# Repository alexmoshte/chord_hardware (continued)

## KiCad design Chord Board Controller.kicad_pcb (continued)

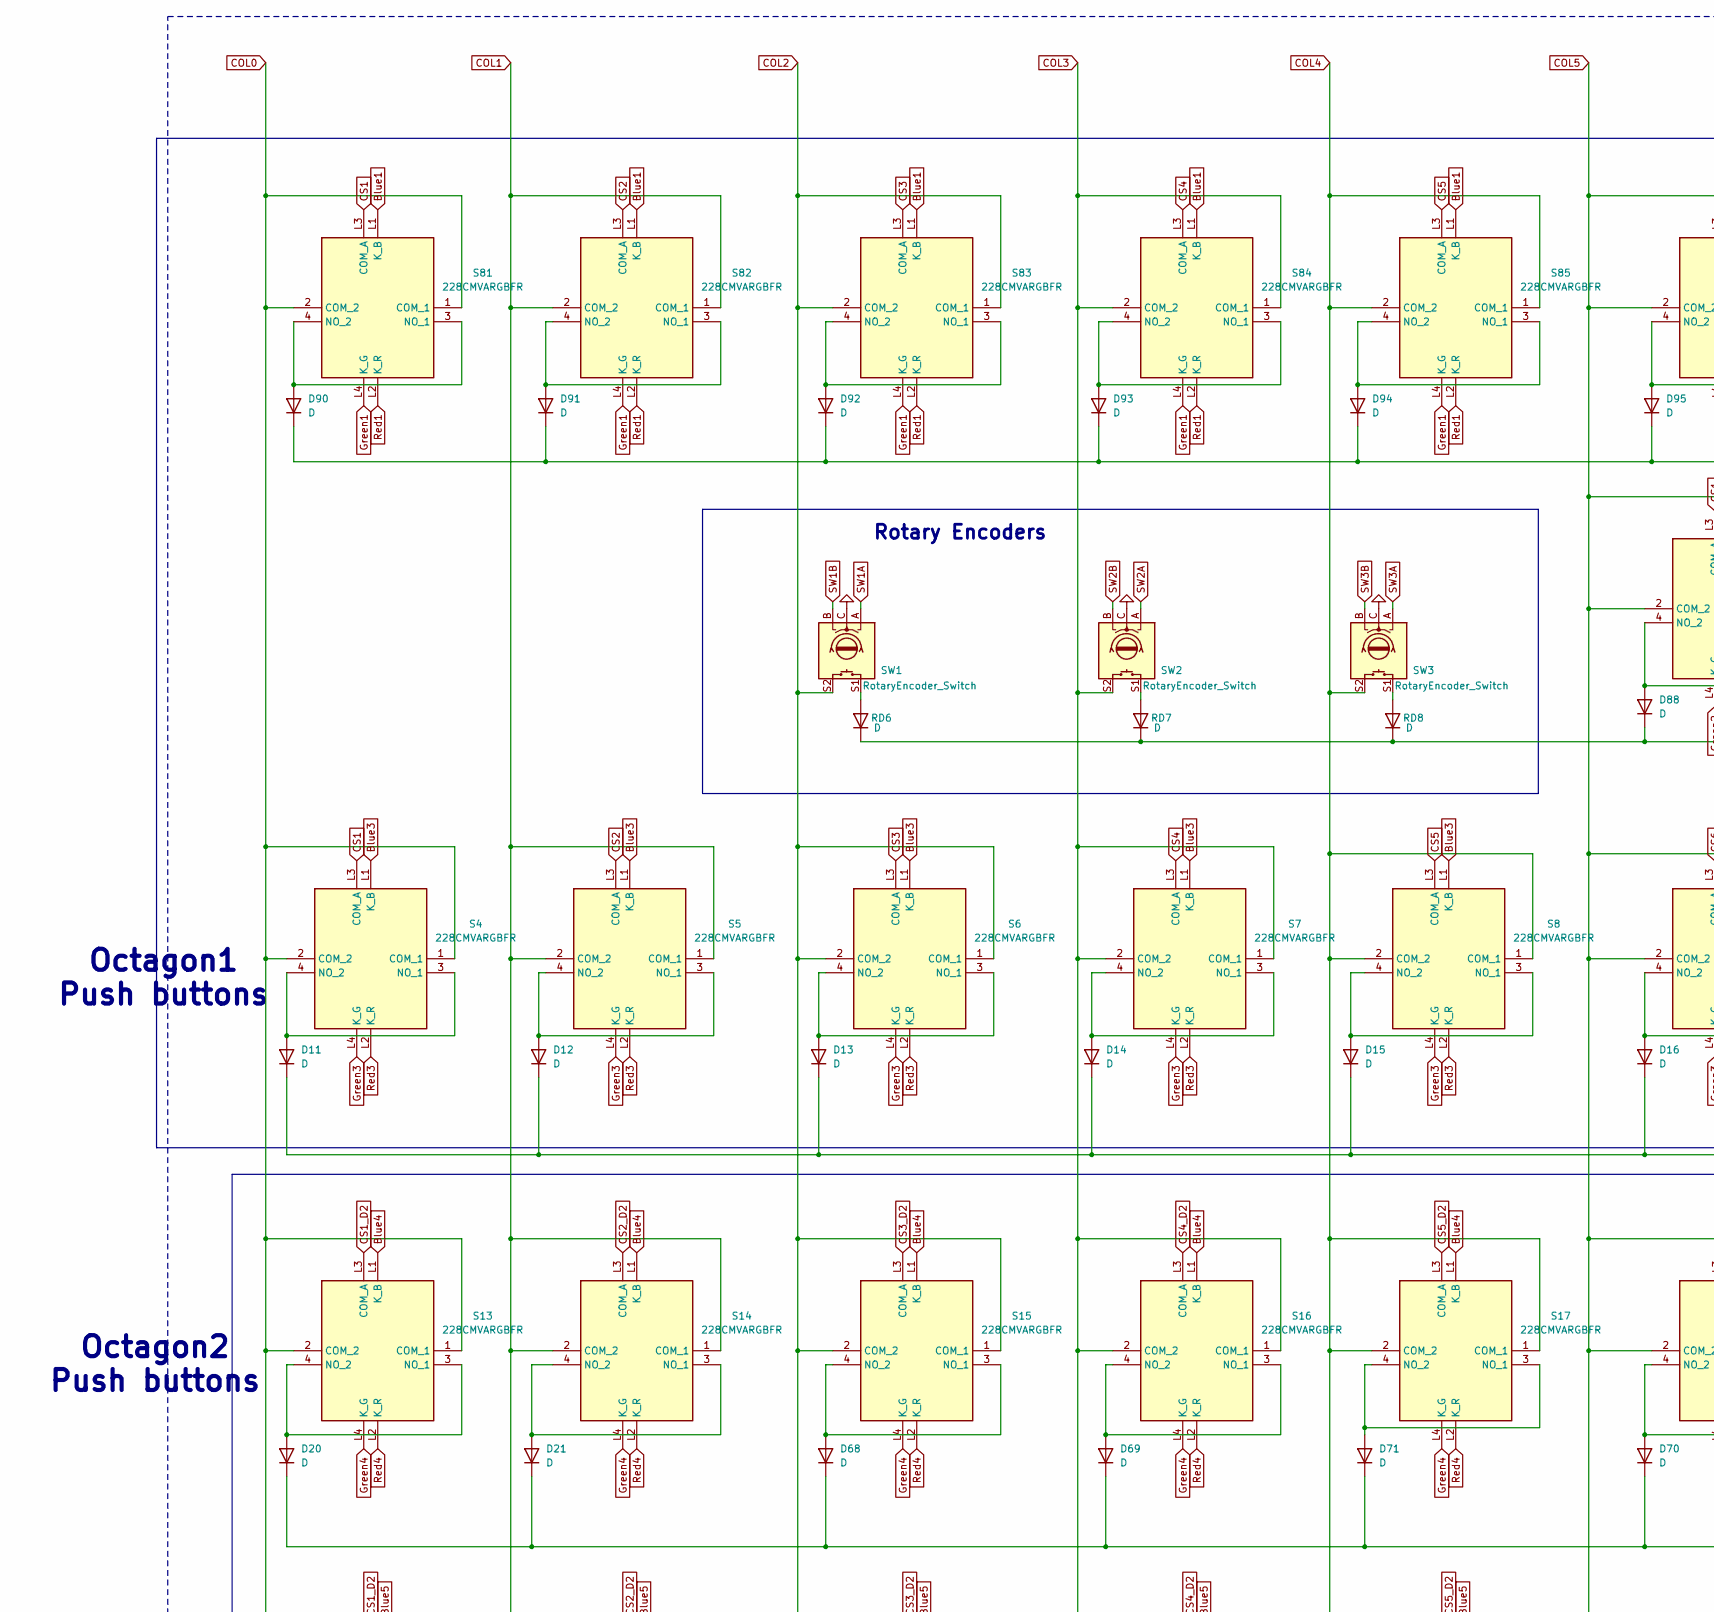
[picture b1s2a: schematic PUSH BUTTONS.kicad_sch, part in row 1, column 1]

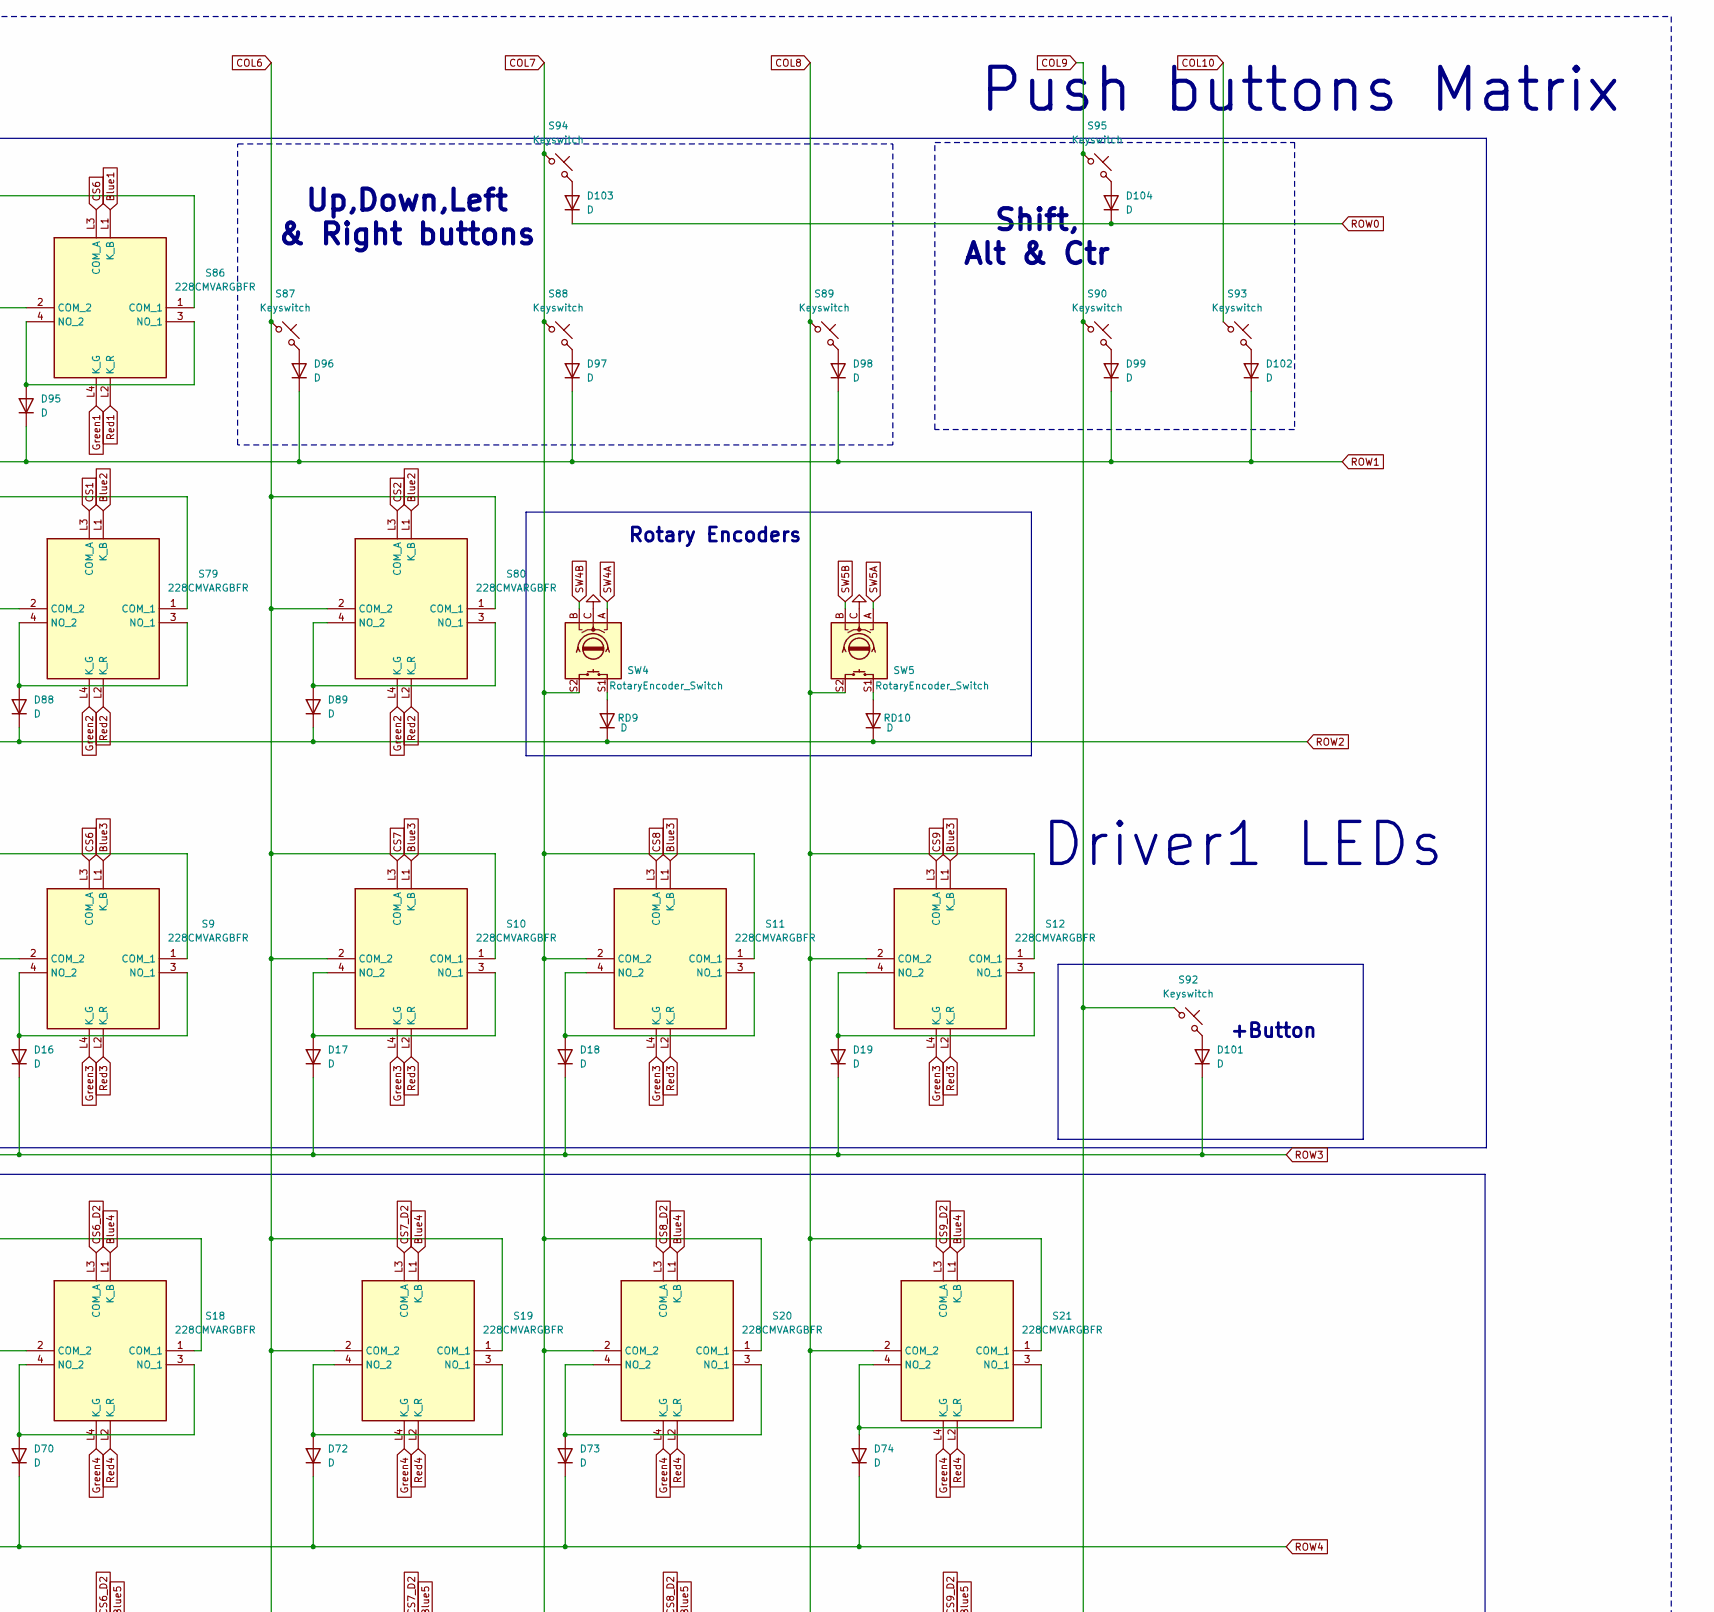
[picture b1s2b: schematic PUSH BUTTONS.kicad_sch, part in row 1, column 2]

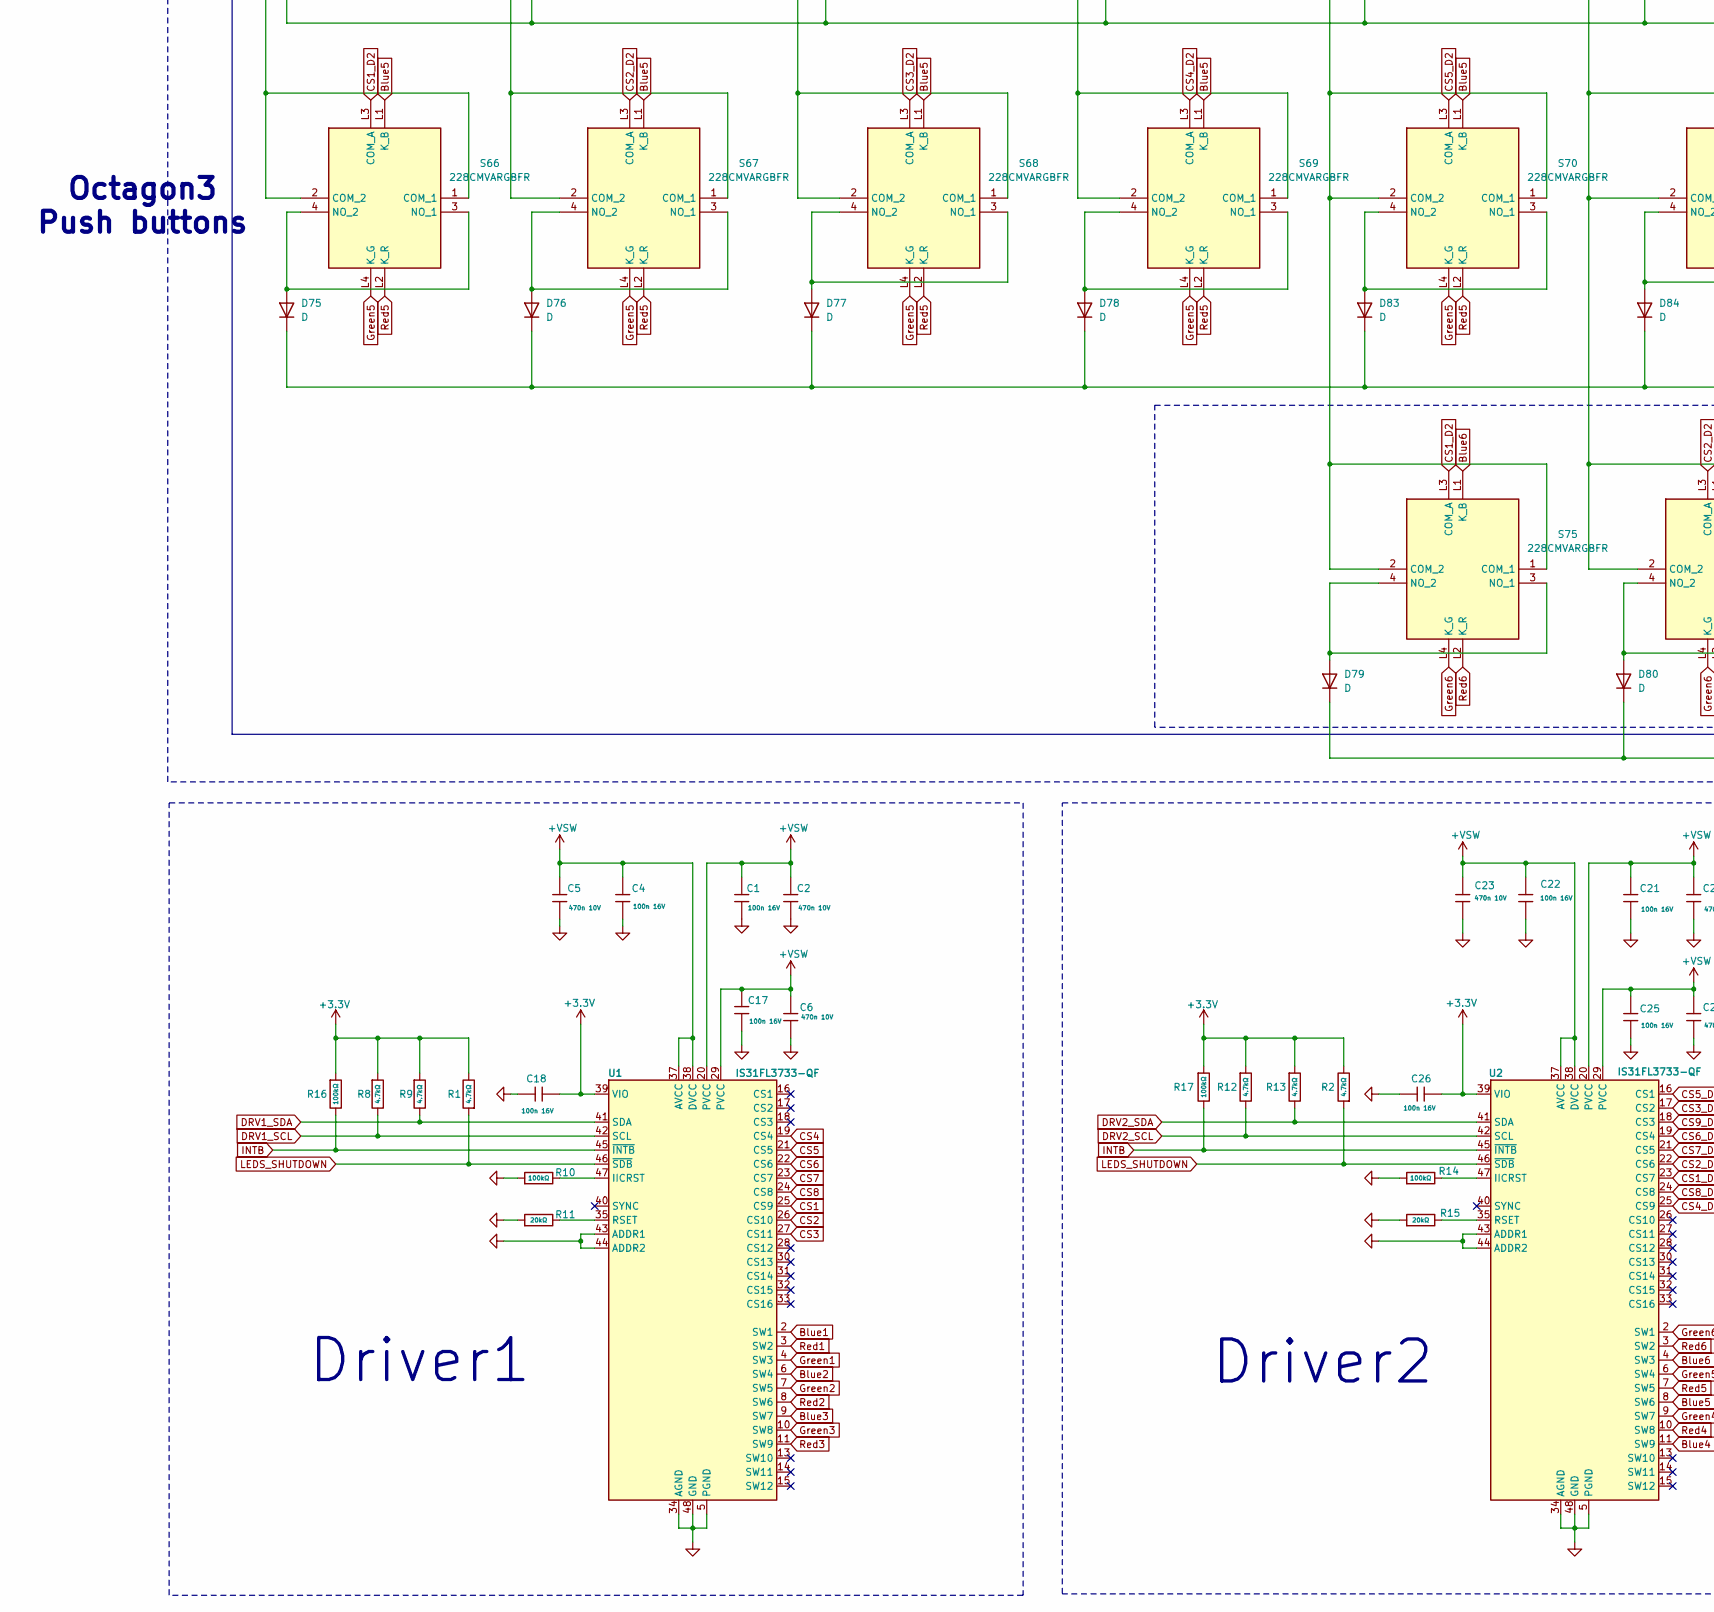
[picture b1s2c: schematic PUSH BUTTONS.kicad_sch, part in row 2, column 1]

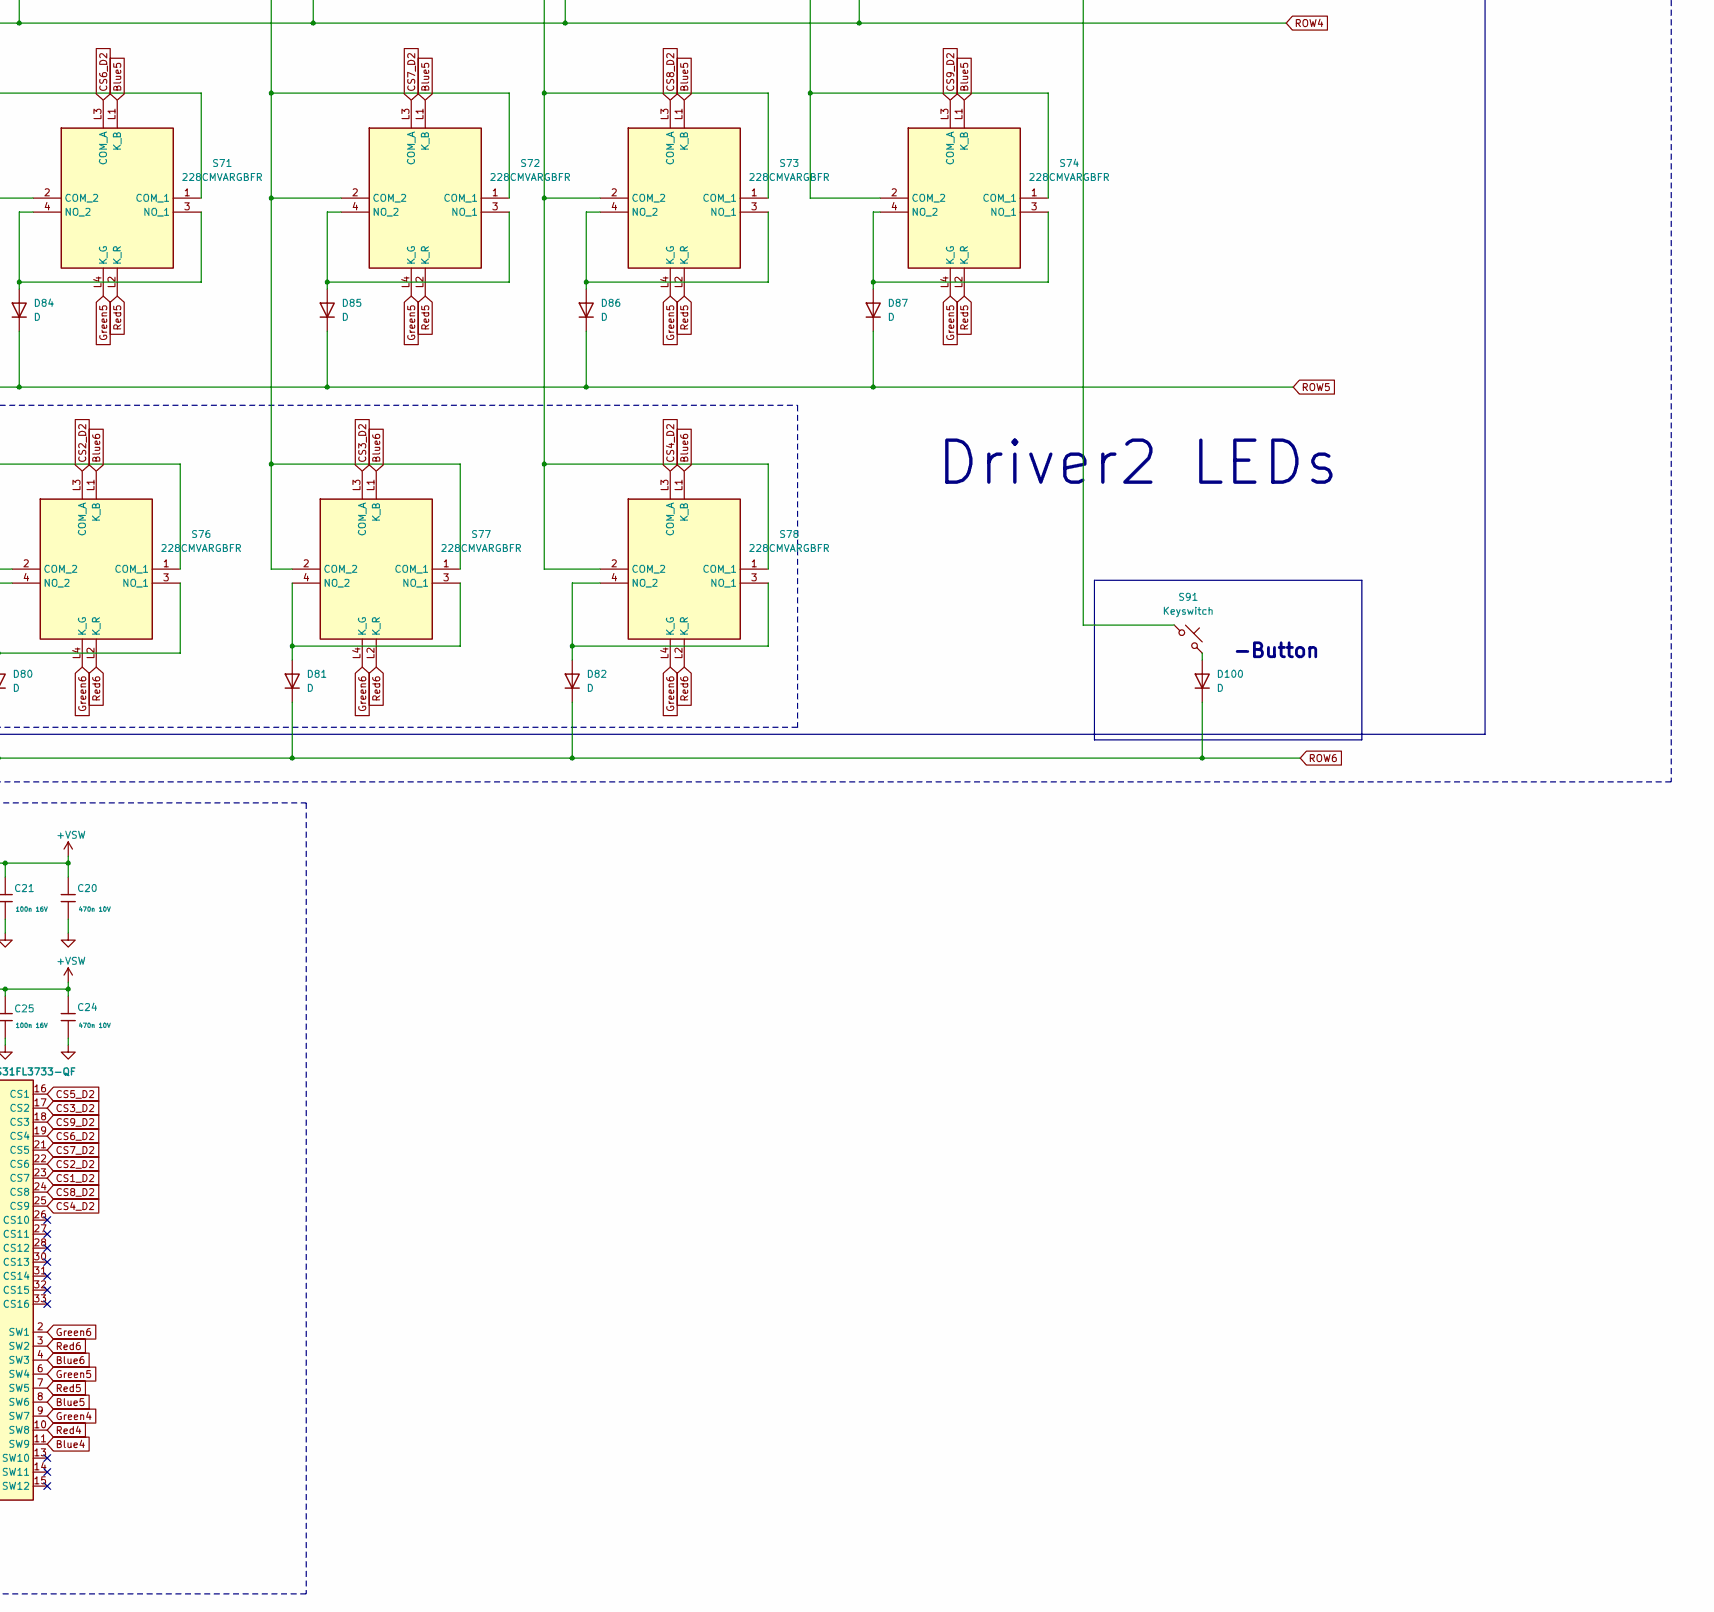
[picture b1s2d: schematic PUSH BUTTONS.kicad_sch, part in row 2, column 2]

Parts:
C1: 100n 16V; C_0603; Voltage Rated 6.3V; Tolerance ±20%; Part CL21A476MQYNNNE; LCSC C16780
C2, C5, C6, C20, C23, C24: 470n 10V; C_0402; Voltage Rated 10V; Tolerance ±10%; Part CL05A474KP5NNNC; LCSC C47339
C4, C17, C18, C21, C22, C25, C26: 100n 16V; C_0402; Voltage Rated 16V; Tolerance ±10%; Part CL05B104KO5NNNC; LCSC C1525
D11, D12, D13, D14, D15, D16, D17, D18, D19, D20, D21, D68, D69, D70, D71, D72, D73, D74, D75, D76, D77, D78, D79, D80, D81, D82, D83, D84, D85, D86, D87, D88, D89, D90, D91, D92, D93, D94, D95, D96, D97, D98, D99, D100, D101, D102, D103, D104: D; D_SOD-123; MFR.Part # SOD1F7; JLCPCB part# C33221
R1, R2, R8, R9, R12, R13: 4.7kΩ; R_0402; Overload Voltage (Max) 50V; Tolerance ±1%; Part 0402WGF4701TCE; LCSC C25900
R10, R14: 100kΩ; R_0402; Overload Voltage (Max) 50V; Tolerance ±1%; Part 0402WGF1003TCE; LCSC C25741
R11, R15: 20kΩ; R_0402; Overload Voltage (Max) 50V; Tolerance ±1%; Part 0402WGF2002TCE; LCSC C25765
R16, R17: 100kΩ; R_0603; Overload Voltage (Max) 75V; Tolerance ±1%; Part 0603WAF1003T5E; LCSC C25803
RD6, RD7, RD8, RD9, RD10: D; D_SOD-123
S4, S5, S6, S7, S8, S9, S10, S11, S12, S13, S14, S15, S16, S17, S18, S19, S20, S21, S66, S67, S68, S69, S70, S71, S72, S73, S74, S75, S76, S77, S78, S79, S80, S81, S82, S83, S84, S85, S86: 228CMVARGBFR; Mouser Part Number 774-228CMVARGBFR
S87, S88, S89, S90, S91, S92, S93, S94, S95: Keyswitch; SW_PUSH_6mm; MFR.Part # ZX-QC66-6.5CJ; JLCPCB part# C7470130
SW1, SW2, SW3, SW4, SW5: RotaryEncoder_Switch; ROT_Alps_EC11E-Switch
U1, U2: IS31FL3733-QF; QFN-48-1EP_6x6mm_P0.4mm_EP4.2x4.2mm

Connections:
+3.3V: C18.2, C26.2, R1.2, R2.2, R8.1, R9.1, R12.1, R13.1, R16.1, R17.1, U1.39 (VIO), U2.39 (VIO); also elsewhere on the board
+VSW: C1.1, C2.1, C4.1, C5.1, C6.1, C17.1, C20.1, C21.1, C22.1, C23.1, C24.1, C25.1, U1.20 (PVCC), U1.29 (PVCC), U1.37 (AVCC), U1.38 (DVCC), U2.20 (PVCC), U2.29 (PVCC), U2.37 (AVCC), U2.38 (DVCC); also elsewhere on the board
Blue1: S81.L1 (K_B), S82.L1 (K_B), S83.L1 (K_B), S84.L1 (K_B), S85.L1 (K_B), S86.L1 (K_B), U1.2 (SW1)
Blue2: S79.L1 (K_B), S80.L1 (K_B), U1.6 (SW4)
Blue3: S4.L1 (K_B), S5.L1 (K_B), S6.L1 (K_B), S7.L1 (K_B), S8.L1 (K_B), S9.L1 (K_B), S10.L1 (K_B), S11.L1 (K_B), S12.L1 (K_B), U1.9 (SW7)
Blue4: S13.L1 (K_B), S14.L1 (K_B), S15.L1 (K_B), S16.L1 (K_B), S17.L1 (K_B), S18.L1 (K_B), S19.L1 (K_B), S20.L1 (K_B), S21.L1 (K_B), U2.11 (SW9)
Blue5: S66.L1 (K_B), S67.L1 (K_B), S68.L1 (K_B), S69.L1 (K_B), S70.L1 (K_B), S71.L1 (K_B), S72.L1 (K_B), S73.L1 (K_B), S74.L1 (K_B), U2.8 (SW6)
Blue6: S75.L1 (K_B), S76.L1 (K_B), S77.L1 (K_B), S78.L1 (K_B), U2.4 (SW3)
COL0: S4.1 (COM_1), S4.2 (COM_2), S13.1 (COM_1), S13.2 (COM_2), S66.1 (COM_1), S66.2 (COM_2), S81.1 (COM_1), S81.2 (COM_2); also elsewhere on the board
COL1: S5.1 (COM_1), S5.2 (COM_2), S14.1 (COM_1), S14.2 (COM_2), S67.1 (COM_1), S67.2 (COM_2), S82.1 (COM_1), S82.2 (COM_2); also elsewhere on the board
COL2: S6.1 (COM_1), S6.2 (COM_2), S15.1 (COM_1), S15.2 (COM_2), S68.1 (COM_1), S68.2 (COM_2), S83.1 (COM_1), S83.2 (COM_2), SW1.S2; also elsewhere on the board
COL3: S7.1 (COM_1), S7.2 (COM_2), S16.1 (COM_1), S16.2 (COM_2), S69.1 (COM_1), S69.2 (COM_2), S84.1 (COM_1), S84.2 (COM_2), SW2.S2; also elsewhere on the board
COL4: S8.1 (COM_1), S8.2 (COM_2), S17.1 (COM_1), S17.2 (COM_2), S70.1 (COM_1), S70.2 (COM_2), S75.1 (COM_1), S75.2 (COM_2), S85.1 (COM_1), S85.2 (COM_2), SW3.S2; also elsewhere on the board
COL5: S9.1 (COM_1), S9.2 (COM_2), S18.1 (COM_1), S18.2 (COM_2), S71.1 (COM_1), S71.2 (COM_2), S76.1 (COM_1), S76.2 (COM_2), S79.1 (COM_1), S79.2 (COM_2), S86.1 (COM_1), S86.2 (COM_2); also elsewhere on the board
COL6: S10.1 (COM_1), S10.2 (COM_2), S19.1 (COM_1), S19.2 (COM_2), S72.1 (COM_1), S72.2 (COM_2), S77.1 (COM_1), S77.2 (COM_2), S80.1 (COM_1), S80.2 (COM_2), S87.1; also elsewhere on the board
COL7: S11.1 (COM_1), S11.2 (COM_2), S20.1 (COM_1), S20.2 (COM_2), S73.1 (COM_1), S73.2 (COM_2), S78.1 (COM_1), S78.2 (COM_2), S88.1, S94.1, SW4.S2; also elsewhere on the board
COL8: S12.1 (COM_1), S12.2 (COM_2), S21.1 (COM_1), S21.2 (COM_2), S74.1 (COM_1), S74.2 (COM_2), S89.1, SW5.S2; also elsewhere on the board
COL9: S90.1, S91.1, S92.1, S95.1; also elsewhere on the board
COL10: S93.1; also elsewhere on the board
CS1: S4.L3 (COM_A), S79.L3 (COM_A), S81.L3 (COM_A), U1.25 (CS9)
CS1_D2: S13.L3 (COM_A), S66.L3 (COM_A), S75.L3 (COM_A), U2.23 (CS7)
CS2: S5.L3 (COM_A), S80.L3 (COM_A), S82.L3 (COM_A), U1.26 (CS10)
CS2_D2: S14.L3 (COM_A), S67.L3 (COM_A), S76.L3 (COM_A), U2.22 (CS6)
CS3: S6.L3 (COM_A), S83.L3 (COM_A), U1.27 (CS11)
CS3_D2: S15.L3 (COM_A), S68.L3 (COM_A), S77.L3 (COM_A), U2.17 (CS2)
CS4: S7.L3 (COM_A), S84.L3 (COM_A), U1.19 (CS4)
CS4_D2: S16.L3 (COM_A), S69.L3 (COM_A), S78.L3 (COM_A), U2.25 (CS9)
CS5: S8.L3 (COM_A), S85.L3 (COM_A), U1.21 (CS5)
CS5_D2: S17.L3 (COM_A), S70.L3 (COM_A), U2.16 (CS1)
CS6: S9.L3 (COM_A), S86.L3 (COM_A), U1.22 (CS6)
CS6_D2: S18.L3 (COM_A), S71.L3 (COM_A), U2.19 (CS4)
CS7: S10.L3 (COM_A), U1.23 (CS7)
CS7_D2: S19.L3 (COM_A), S72.L3 (COM_A), U2.21 (CS5)
CS8: S11.L3 (COM_A), U1.24 (CS8)
CS8_D2: S20.L3 (COM_A), S73.L3 (COM_A), U2.24 (CS8)
CS9: S12.L3 (COM_A)
CS9_D2: S21.L3 (COM_A), S74.L3 (COM_A), U2.18 (CS3)
DRV1_SCL: R8.2, U1.42 (SCL); also elsewhere on the board
DRV1_SDA: R9.2, U1.41 (SDA); also elsewhere on the board
DRV2_SCL: R12.2, U2.42 (SCL); also elsewhere on the board
DRV2_SDA: R13.2, U2.41 (SDA); also elsewhere on the board
GND: C1.2, C2.2, C4.2, C5.2, C6.2, C17.2, C18.1, C20.2, C21.2, C22.2, C23.2, C24.2, C25.2, C26.1, R10.1, R11.1, R14.1, R15.1, SW1.C, SW2.C, SW3.C, SW4.C, SW5.C, U1.5 (PGND), U1.12 (PGND), U1.34 (AGND), U1.43 (ADDR1), U1.44 (ADDR2), U1.48 (GND), U1.49 (GND), U2.5 (PGND), U2.12 (PGND), U2.34 (AGND), U2.43 (ADDR1), U2.44 (ADDR2), U2.48 (GND), U2.49 (GND); also elsewhere on the board
Green1: S81.L4 (K_G), S82.L4 (K_G), S83.L4 (K_G), S84.L4 (K_G), S85.L4 (K_G), S86.L4 (K_G), U1.4 (SW3)
Green2: S79.L4 (K_G), S80.L4 (K_G), U1.7 (SW5)
Green3: S4.L4 (K_G), S5.L4 (K_G), S6.L4 (K_G), S7.L4 (K_G), S8.L4 (K_G), S9.L4 (K_G), S10.L4 (K_G), S11.L4 (K_G), S12.L4 (K_G), U1.10 (SW8)
Green4: S13.L4 (K_G), S14.L4 (K_G), S15.L4 (K_G), S16.L4 (K_G), S17.L4 (K_G), S18.L4 (K_G), S19.L4 (K_G), S20.L4 (K_G), S21.L4 (K_G), U2.9 (SW7)
Green5: S66.L4 (K_G), S67.L4 (K_G), S68.L4 (K_G), S69.L4 (K_G), S70.L4 (K_G), S71.L4 (K_G), S72.L4 (K_G), S73.L4 (K_G), S74.L4 (K_G), U2.6 (SW4)
Green6: S75.L4 (K_G), S76.L4 (K_G), S77.L4 (K_G), S78.L4 (K_G), U2.2 (SW1)
INTB: R16.2, R17.2, U1.45 (~INTB), U2.45 (~INTB); also elsewhere on the board
LEDS_SHUTDOWN: R1.1, R2.1, U1.46 (~SDB), U2.46 (~SDB); also elsewhere on the board
unnamed: D11.2 (A), S4.3 (NO_1), S4.4 (NO_2)
unnamed: D12.2 (A), S5.3 (NO_1), S5.4 (NO_2)
unnamed: D13.2 (A), S6.3 (NO_1), S6.4 (NO_2)
unnamed: D14.2 (A), S7.3 (NO_1), S7.4 (NO_2)
unnamed: D15.2 (A), S8.3 (NO_1), S8.4 (NO_2)
unnamed: D16.2 (A), S9.3 (NO_1), S9.4 (NO_2)
unnamed: D17.2 (A), S10.3 (NO_1), S10.4 (NO_2)
unnamed: D18.2 (A), S11.3 (NO_1), S11.4 (NO_2)
unnamed: D19.2 (A), S12.3 (NO_1), S12.4 (NO_2)
unnamed: D20.2 (A), S13.3 (NO_1), S13.4 (NO_2)
unnamed: D21.2 (A), S14.3 (NO_1), S14.4 (NO_2)
unnamed: D68.2 (A), S15.3 (NO_1), S15.4 (NO_2)
unnamed: D69.2 (A), S16.3 (NO_1), S16.4 (NO_2)
unnamed: D70.2 (A), S18.3 (NO_1), S18.4 (NO_2)
unnamed: D71.2 (A), S17.3 (NO_1), S17.4 (NO_2)
unnamed: D72.2 (A), S19.3 (NO_1), S19.4 (NO_2)
unnamed: D73.2 (A), S20.3 (NO_1), S20.4 (NO_2)
unnamed: D74.2 (A), S21.3 (NO_1), S21.4 (NO_2)
unnamed: D75.2 (A), S66.3 (NO_1), S66.4 (NO_2)
unnamed: D76.2 (A), S67.3 (NO_1), S67.4 (NO_2)
unnamed: D77.2 (A), S68.3 (NO_1), S68.4 (NO_2)
unnamed: D78.2 (A), S69.3 (NO_1), S69.4 (NO_2)
unnamed: D79.2 (A), S75.3 (NO_1), S75.4 (NO_2)
unnamed: D80.2 (A), S76.3 (NO_1), S76.4 (NO_2)
unnamed: D81.2 (A), S77.3 (NO_1), S77.4 (NO_2)
unnamed: D82.2 (A), S78.3 (NO_1), S78.4 (NO_2)
unnamed: D83.2 (A), S70.3 (NO_1), S70.4 (NO_2)
unnamed: D84.2 (A), S71.3 (NO_1), S71.4 (NO_2)
unnamed: D85.2 (A), S72.3 (NO_1), S72.4 (NO_2)
unnamed: D86.2 (A), S73.3 (NO_1), S73.4 (NO_2)
unnamed: D87.2 (A), S74.3 (NO_1), S74.4 (NO_2)
unnamed: D88.2 (A), S79.3 (NO_1), S79.4 (NO_2)
unnamed: D89.2 (A), S80.3 (NO_1), S80.4 (NO_2)
unnamed: D90.2 (A), S81.3 (NO_1), S81.4 (NO_2)
unnamed: D91.2 (A), S82.3 (NO_1), S82.4 (NO_2)
unnamed: D92.2 (A), S83.3 (NO_1), S83.4 (NO_2)
unnamed: D93.2 (A), S84.3 (NO_1), S84.4 (NO_2)
unnamed: D94.2 (A), S85.3 (NO_1), S85.4 (NO_2)
unnamed: D95.2 (A), S86.3 (NO_1), S86.4 (NO_2)
unnamed: D96.2 (A), S87.2
unnamed: D97.2 (A), S88.2
unnamed: D98.2 (A), S89.2
unnamed: D99.2 (A), S90.2
unnamed: D100.2 (A), S91.2
unnamed: D101.2 (A), S92.2
unnamed: D102.2 (A), S93.2
unnamed: D103.2 (A), S94.2
unnamed: D104.2 (A), S95.2
unnamed: RD6.2 (A), SW1.S1
unnamed: RD7.2 (A), SW2.S1
unnamed: RD8.2 (A), SW3.S1
unnamed: RD9.2 (A), SW4.S1
unnamed: RD10.2 (A), SW5.S1
unnamed: R10.2, U1.47 (IICRST)
unnamed: R11.2, U1.35 (RSET)
unnamed: R14.2, U2.47 (IICRST)
unnamed: R15.2, U2.35 (RSET)
ROW0: D103.1 (K), D104.1 (K); also elsewhere on the board
ROW1: D90.1 (K), D91.1 (K), D92.1 (K), D93.1 (K), D94.1 (K), D95.1 (K), D96.1 (K), D97.1 (K), D98.1 (K), D99.1 (K), D102.1 (K); also elsewhere on the board
ROW2: D88.1 (K), D89.1 (K), RD6.1 (K), RD7.1 (K), RD8.1 (K), RD9.1 (K), RD10.1 (K); also elsewhere on the board
ROW3: D11.1 (K), D12.1 (K), D13.1 (K), D14.1 (K), D15.1 (K), D16.1 (K), D17.1 (K), D18.1 (K), D19.1 (K), D101.1 (K); also elsewhere on the board
ROW4: D20.1 (K), D21.1 (K), D68.1 (K), D69.1 (K), D70.1 (K), D71.1 (K), D72.1 (K), D73.1 (K), D74.1 (K); also elsewhere on the board
ROW5: D75.1 (K), D76.1 (K), D77.1 (K), D78.1 (K), D83.1 (K), D84.1 (K), D85.1 (K), D86.1 (K), D87.1 (K); also elsewhere on the board
ROW6: D79.1 (K), D80.1 (K), D81.1 (K), D82.1 (K), D100.1 (K); also elsewhere on the board
Red1: S81.L2 (K_R), S82.L2 (K_R), S83.L2 (K_R), S84.L2 (K_R), S85.L2 (K_R), S86.L2 (K_R), U1.3 (SW2)
Red2: S79.L2 (K_R), S80.L2 (K_R), U1.8 (SW6)
Red3: S4.L2 (K_R), S5.L2 (K_R), S6.L2 (K_R), S7.L2 (K_R), S8.L2 (K_R), S9.L2 (K_R), S10.L2 (K_R), S11.L2 (K_R), S12.L2 (K_R), U1.11 (SW9)
Red4: S13.L2 (K_R), S14.L2 (K_R), S15.L2 (K_R), S16.L2 (K_R), S17.L2 (K_R), S18.L2 (K_R), S19.L2 (K_R), S20.L2 (K_R), S21.L2 (K_R), U2.10 (SW8)
Red5: S66.L2 (K_R), S67.L2 (K_R), S68.L2 (K_R), S69.L2 (K_R), S70.L2 (K_R), S71.L2 (K_R), S72.L2 (K_R), S73.L2 (K_R), S74.L2 (K_R), U2.7 (SW5)
Red6: S75.L2 (K_R), S76.L2 (K_R), S77.L2 (K_R), S78.L2 (K_R), U2.3 (SW2)
SW1A: SW1.A; also elsewhere on the board
SW1B: SW1.B; also elsewhere on the board
SW2A: SW2.A; also elsewhere on the board
SW2B: SW2.B; also elsewhere on the board
SW3A: SW3.A; also elsewhere on the board
SW3B: SW3.B; also elsewhere on the board
SW4A: SW4.A; also elsewhere on the board
SW4B: SW4.B; also elsewhere on the board
SW5A: SW5.A; also elsewhere on the board
SW5B: SW5.B; also elsewhere on the board

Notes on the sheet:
-Button
Rotary Encoders
Shift, Alt & Ctr
Driver1
Driver2
Up,Down,Left & Right buttons
+Button
Octagon2 Push buttons
Driver1 LEDs
Octagon1 Push buttons
Driver2 LEDs
Octagon3 Push buttons
Push buttons Matrix

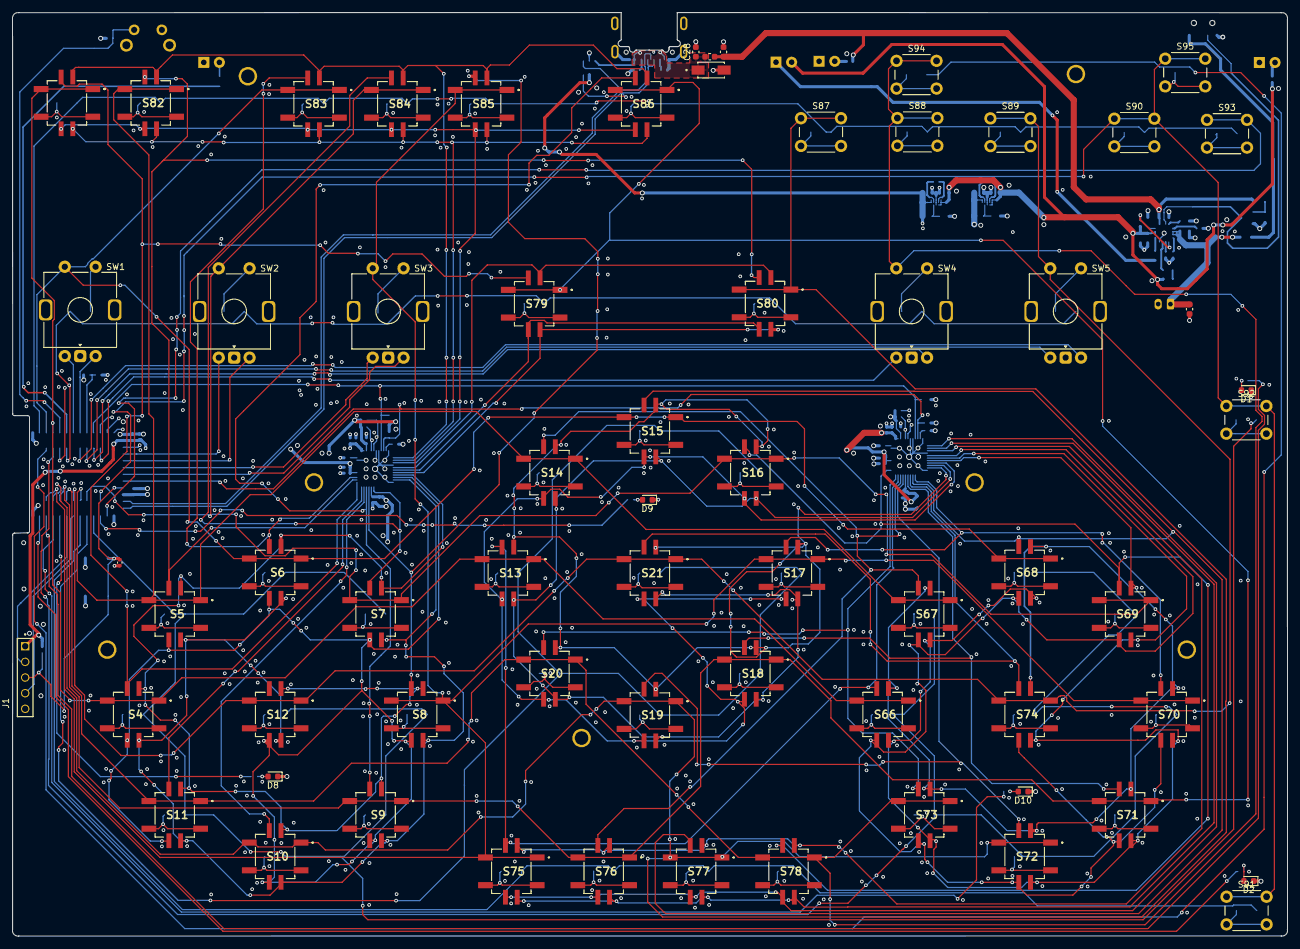
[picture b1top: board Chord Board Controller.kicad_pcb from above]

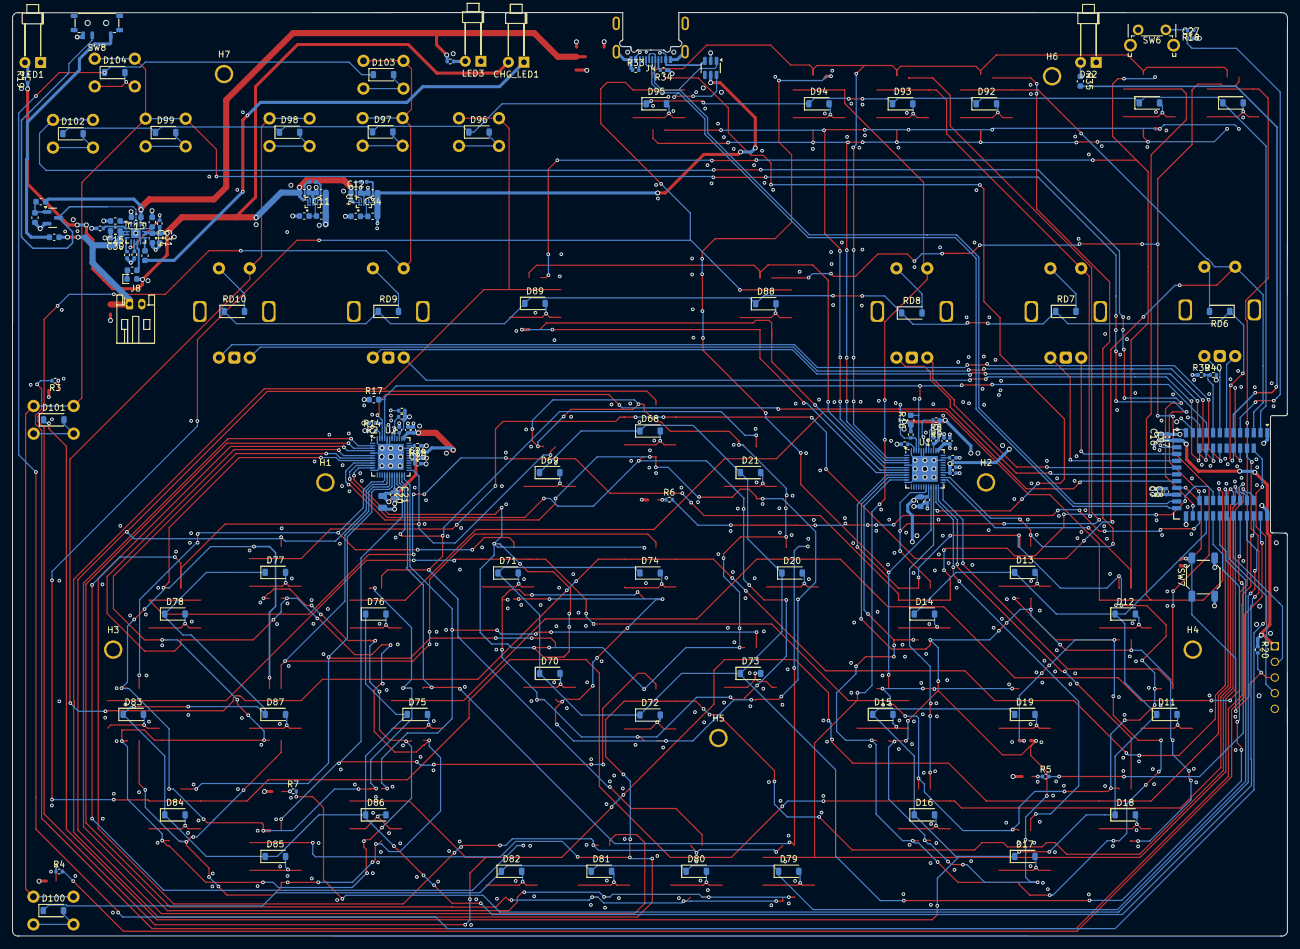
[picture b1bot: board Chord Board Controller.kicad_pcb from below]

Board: 6 copper layers, 207.0 x 149.9 mm, 215 parts (150 on the bottom side), 175 nets.

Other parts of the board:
C19: 47uF; C_0805

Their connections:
+VSW: C19.1; also elsewhere on the board
GND: C19.2; also elsewhere on the board

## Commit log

2025-11-03 schmtcs vsn1
2025-11-04 gnd cutiings rmvd
2025-11-04 power done
2025-11-05 Routing done
2025-11-05 aron review
2025-11-05 post review
